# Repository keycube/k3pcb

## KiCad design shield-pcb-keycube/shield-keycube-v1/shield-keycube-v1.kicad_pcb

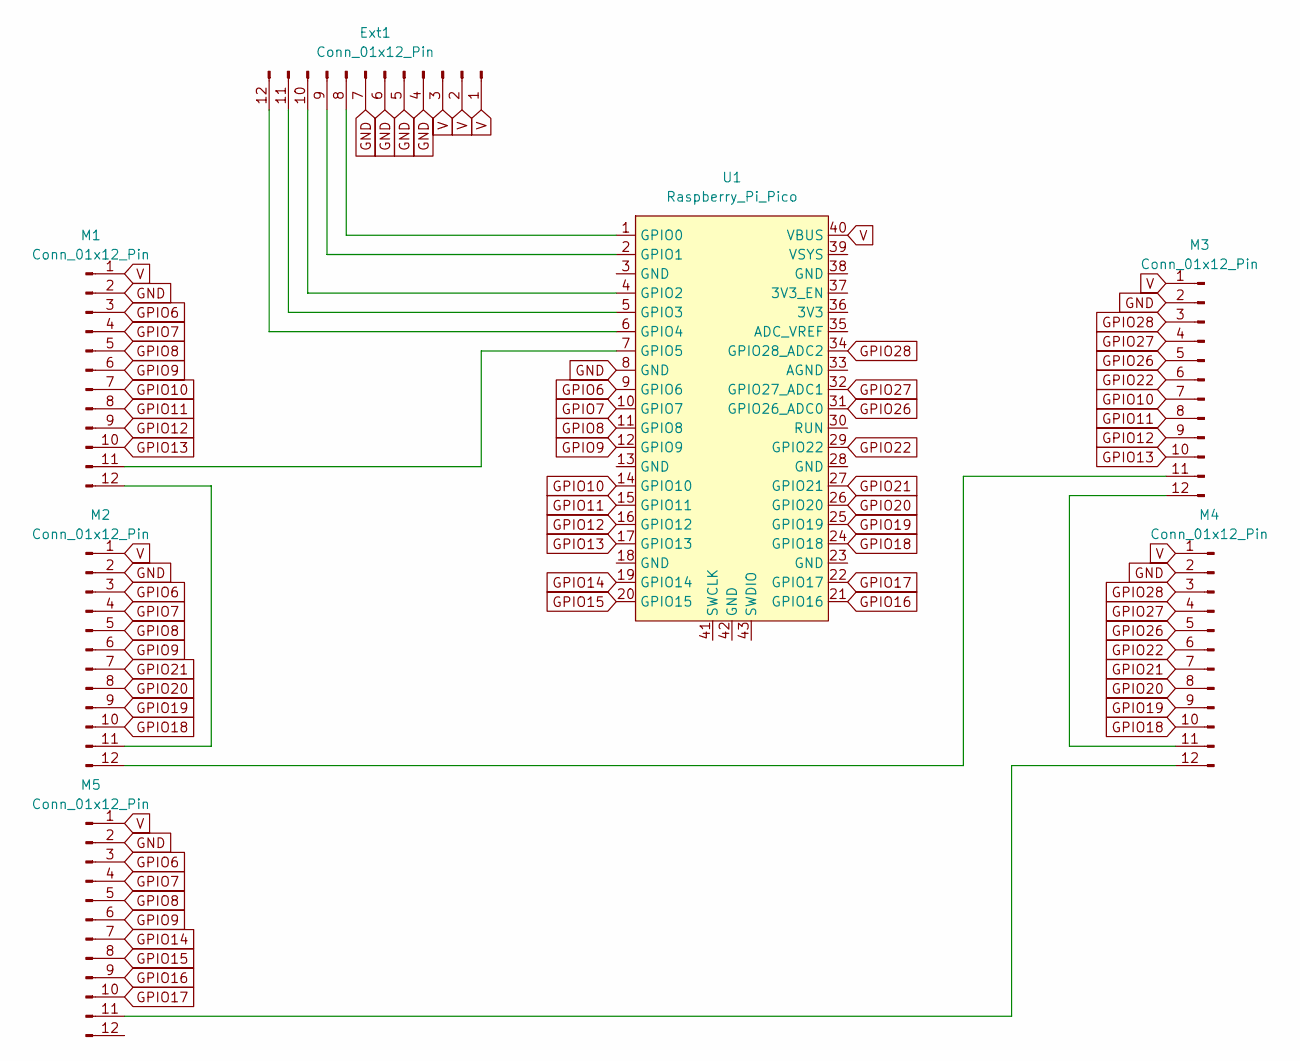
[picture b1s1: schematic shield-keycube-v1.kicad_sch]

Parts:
Ext1: Conn_01x12_Pin; PinHeader_1x12_P2.00mm_Vertical
M1, M2, M3, M4, M5: Conn_01x12_Pin; PinHeader_1x12_P2.00mm_Vertical
U1: Raspberry_Pi_Pico

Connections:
GND: Ext1.4, Ext1.5, Ext1.6, Ext1.7, M1.2, M2.2, M3.2, M4.2, M5.2, U1.8 (GND)
GPIO6: M1.3, M2.3, M5.3, U1.9 (GPIO6)
GPIO7: M1.4, M2.4, M5.4, U1.10 (GPIO7)
GPIO8: M1.5, M2.5, M5.5, U1.11 (GPIO8)
GPIO9: M1.6, M2.6, M5.6, U1.12 (GPIO9)
GPIO10: M1.7, M3.7, U1.14 (GPIO10)
GPIO11: M1.8, M3.8, U1.15 (GPIO11)
GPIO12: M1.9, M3.9, U1.16 (GPIO12)
GPIO13: M1.10, M3.10, U1.17 (GPIO13)
GPIO14: M5.7, U1.19 (GPIO14)
GPIO15: M5.8, U1.20 (GPIO15)
GPIO16: M5.9, U1.21 (GPIO16)
GPIO17: M5.10, U1.22 (GPIO17)
GPIO18: M2.10, M4.10, U1.24 (GPIO18)
GPIO19: M2.9, M4.9, U1.25 (GPIO19)
GPIO20: M2.8, M4.8, U1.26 (GPIO20)
GPIO21: M2.7, M4.7, U1.27 (GPIO21)
GPIO22: M3.6, M4.6, U1.29 (GPIO22)
GPIO26: M3.5, M4.5, U1.31 (GPIO26_ADC0)
GPIO27: M3.4, M4.4, U1.32 (GPIO27_ADC1)
GPIO28: M3.3, M4.3, U1.34 (GPIO28_ADC2)
unnamed: Ext1.8, U1.1 (GPIO0)
unnamed: Ext1.9, U1.2 (GPIO1)
unnamed: Ext1.10, U1.4 (GPIO2)
unnamed: Ext1.11, U1.5 (GPIO3)
unnamed: Ext1.12, U1.6 (GPIO4)
unnamed: M1.11, U1.7 (GPIO5)
unnamed: M1.12, M2.11
unnamed: M2.12, M3.11
unnamed: M3.12, M4.11
unnamed: M4.12, M5.11
V: Ext1.1, Ext1.2, Ext1.3, M1.1, M2.1, M3.1, M4.1, M5.1, U1.40 (VBUS)

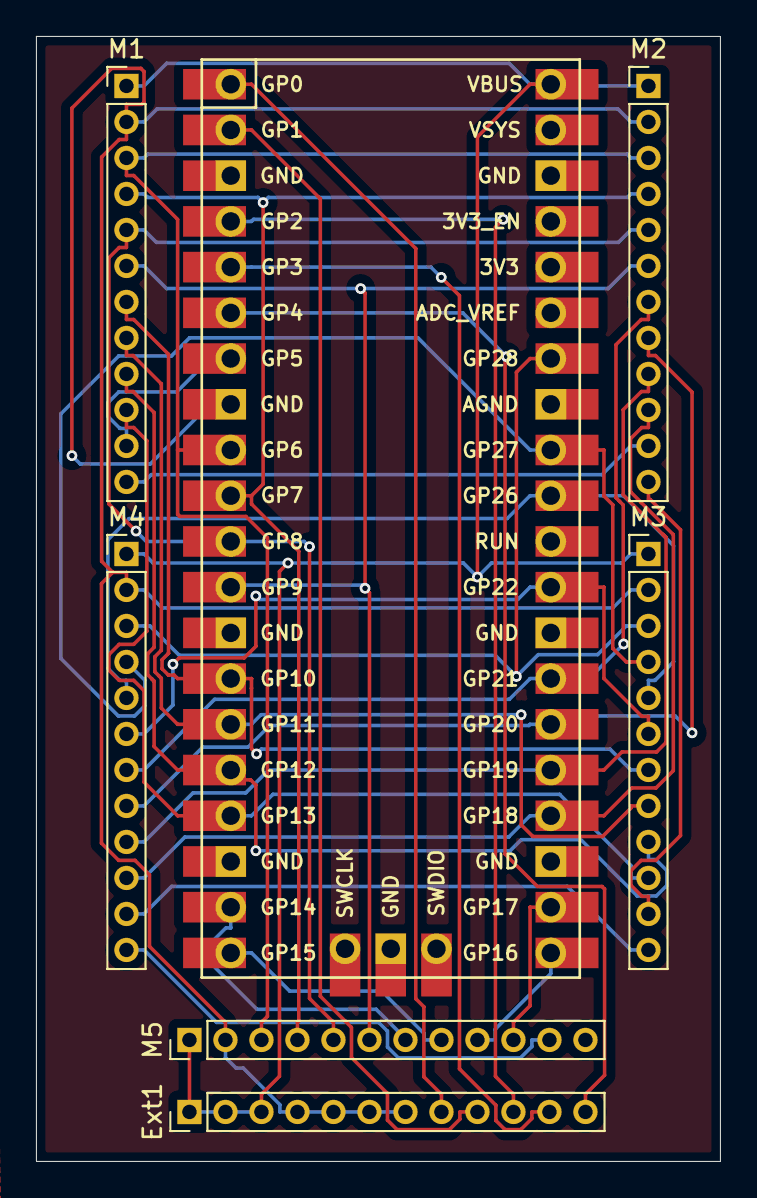
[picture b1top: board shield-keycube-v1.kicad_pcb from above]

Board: 2 copper layers, 38.0 x 62.5 mm, 7 parts (0 on the bottom side), 32 nets.

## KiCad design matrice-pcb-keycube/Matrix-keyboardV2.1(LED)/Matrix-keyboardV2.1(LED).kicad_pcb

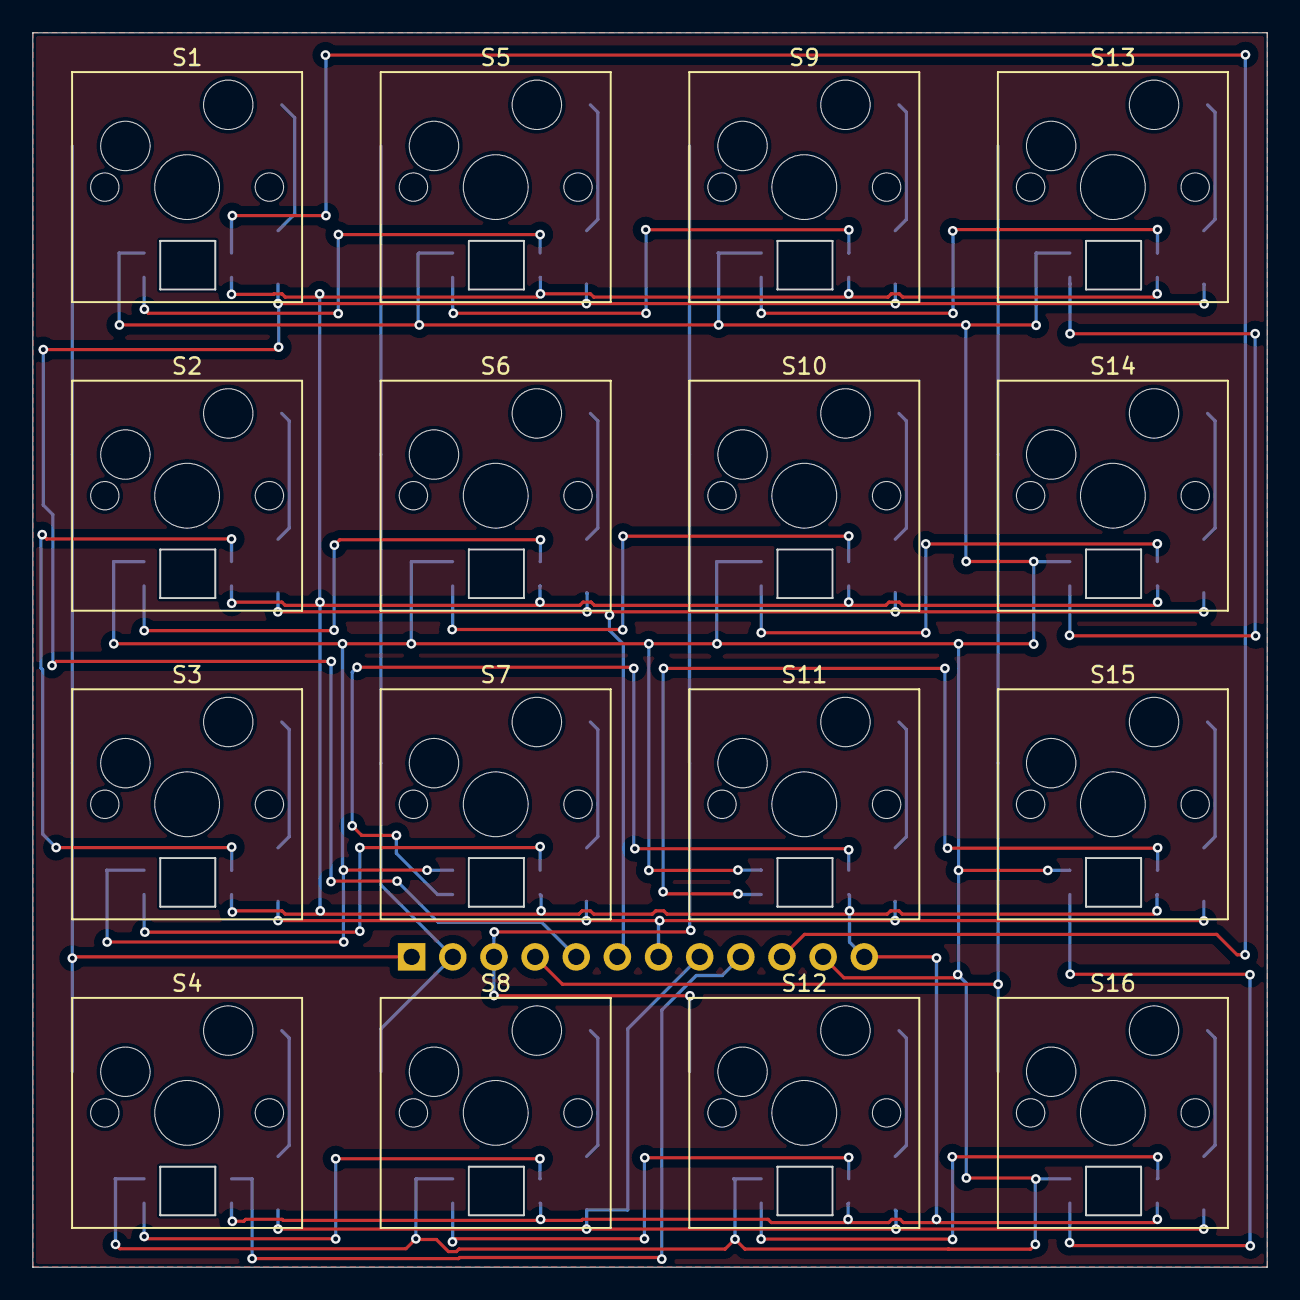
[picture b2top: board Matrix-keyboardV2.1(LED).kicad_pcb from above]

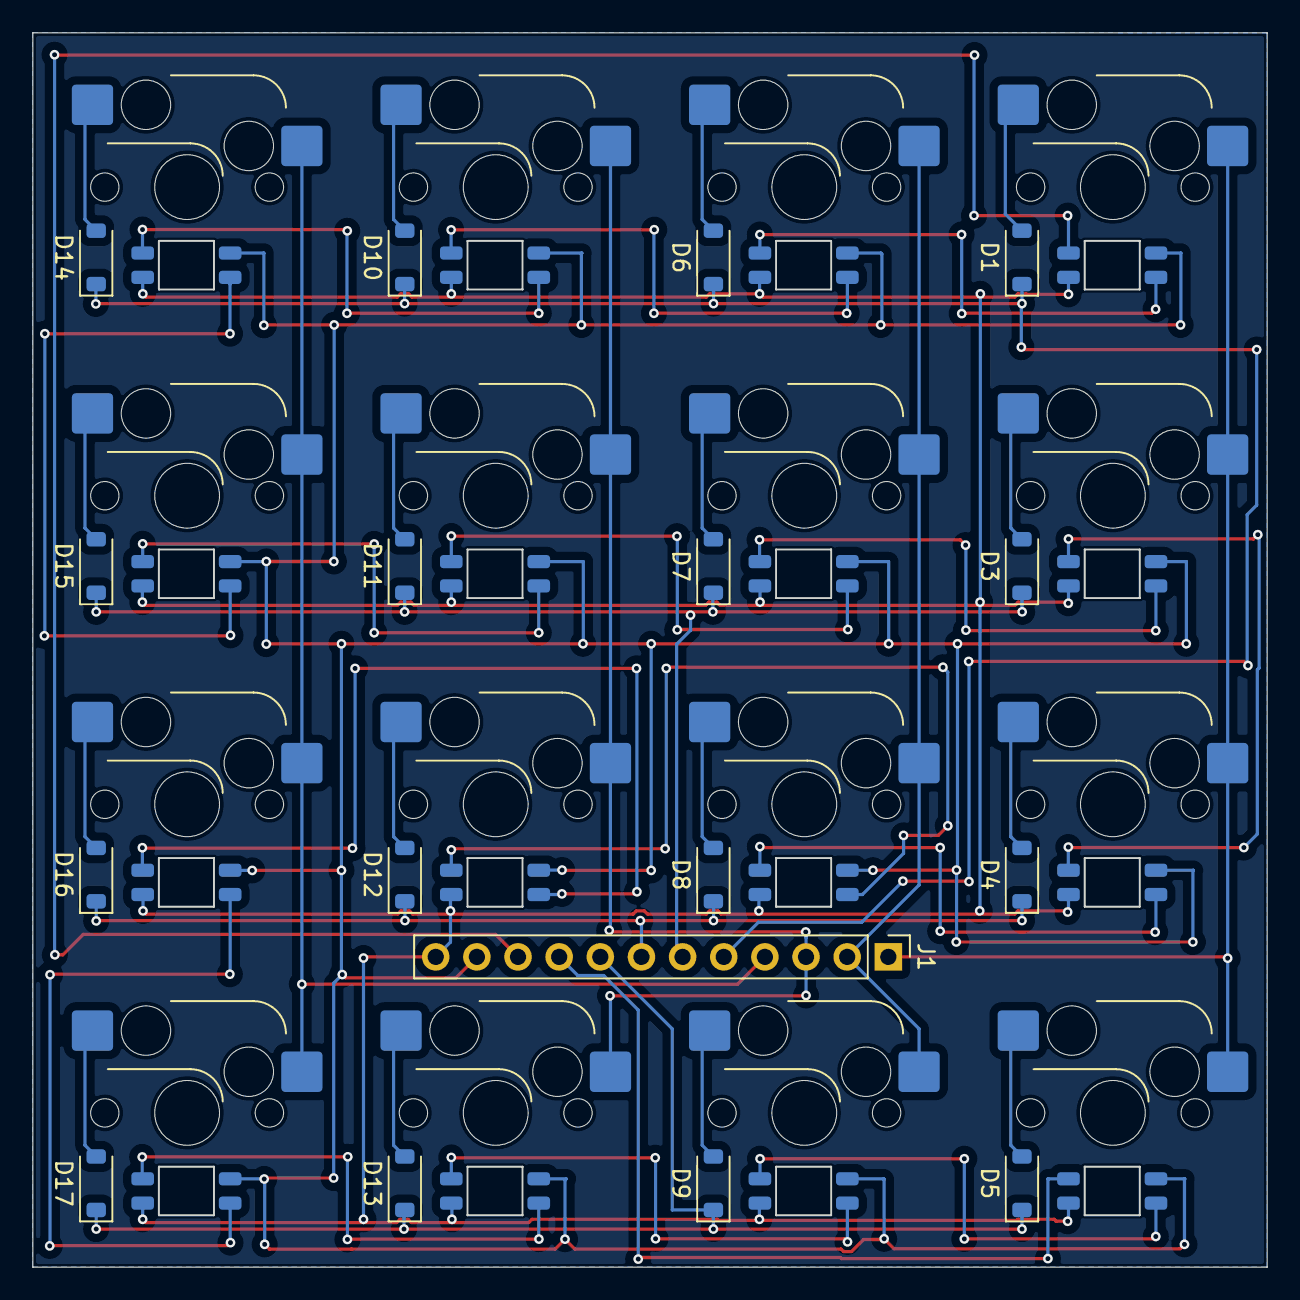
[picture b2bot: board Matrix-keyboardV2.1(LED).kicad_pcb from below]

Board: 2 copper layers, 76.2 x 76.2 mm, 49 parts (33 on the bottom side), 43 nets.

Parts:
D1, D3, D4, D5, D6, D7, D8, D9, D10, D11, D12, D13, D14, D15, D16, D17: 1N4148W; D_SOD-123
D2, D18, D19, D20, D21, D22, D23, D24, D25, D26, D27, D28, D29, D30, D31, D32: LED_SK6812MINI
J1: Conn_01x12_Socket; PinHeader_1x12_P2.54mm_Vertical
S1, S2, S3, S4, S5, S6, S7, S8, S9, S10, S11, S12, S13, S14, S15, S16: Keyswitch; Hotswap_MX_1.00u

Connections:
DIN: D2.4 (DIN), J1.10
DOUT: D26.4 (DIN), J1.9
unnamed: D1.2 (A), S1.2
unnamed: D3.2 (A), S2.2
unnamed: D4.2 (A), S3.2
unnamed: D5.2 (A), S4.2
unnamed: D6.2 (A), S5.2
unnamed: D7.2 (A), S6.2
unnamed: D8.2 (A), S7.2
unnamed: D9.2 (A), S8.2
unnamed: D10.2 (A), S9.2
unnamed: D11.2 (A), S10.2
unnamed: D12.2 (A), S11.2
unnamed: D13.2 (A), S12.2
unnamed: D14.2 (A), S13.2
unnamed: D15.2 (A), S14.2
unnamed: D16.2 (A), S15.2
unnamed: D17.2 (A), S16.2
unnamed: D2.2 (DOUT), D18.4 (DIN)
unnamed: D18.2 (DOUT), D19.4 (DIN)
unnamed: D19.2 (DOUT), D20.4 (DIN)
unnamed: D20.2 (DOUT), D24.2 (DOUT)
unnamed: D21.4 (DIN), D25.4 (DIN)
unnamed: D21.2 (DOUT), D22.4 (DIN)
unnamed: D22.2 (DOUT), D23.4 (DIN)
unnamed: D23.2 (DOUT), D24.4 (DIN)
unnamed: D25.2 (DOUT), D27.4 (DIN)
unnamed: D26.2 (DOUT), D28.4 (DIN)
unnamed: D27.2 (DOUT), D29.4 (DIN)
unnamed: D28.2 (DOUT), D30.4 (DIN)
unnamed: D29.2 (DOUT), D31.4 (DIN)
unnamed: D30.2 (DOUT), D32.4 (DIN)
unnamed: D31.2 (DOUT), D32.2 (DOUT)
VDD: D2.1 (VDD), D18.1 (VDD), D19.1 (VDD), D20.1 (VDD), D21.1 (VDD), D22.1 (VDD), D23.1 (VDD), D24.1 (VDD), D25.1 (VDD), D26.1 (VDD), D27.1 (VDD), D28.1 (VDD), D29.1 (VDD), D30.1 (VDD), D31.1 (VDD), D32.1 (VDD), J1.11
VSS: D2.3 (VSS), D18.3 (VSS), D19.3 (VSS), D20.3 (VSS), D21.3 (VSS), D22.3 (VSS), D23.3 (VSS), D24.3 (VSS), D25.3 (VSS), D26.3 (VSS), D27.3 (VSS), D28.3 (VSS), D29.3 (VSS), D30.3 (VSS), D31.3 (VSS), D32.3 (VSS), J1.12
column 1: J1.1, S1.1, S2.1, S3.1, S4.1
column 2: J1.2, S5.1, S6.1, S7.1, S8.1
column 3: J1.3, S9.1, S10.1, S11.1, S12.1
column 4: J1.4, S13.1, S14.1, S15.1, S16.1
row 1: D1.1 (K), D6.1 (K), D10.1 (K), D14.1 (K), J1.5
row 2: D3.1 (K), D7.1 (K), D11.1 (K), D15.1 (K), J1.6
row 3: D4.1 (K), D8.1 (K), D12.1 (K), D16.1 (K), J1.7
row 4: D5.1 (K), D9.1 (K), D13.1 (K), D17.1 (K), J1.8

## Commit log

2025-04-30 ADD kicad project Matrice and his documentation
2025-05-01 REMOVE zip
2025-05-04 Add shield v1 documentation
2025-05-05 Add shield kicad project. Fix missing line in doc.
2025-05-05 Add video link to docs
